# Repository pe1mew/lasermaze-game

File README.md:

# lasermaze-game
A laser maze game designed for BULA2022 

# Work in progress
This is work in progress. Thing may be added or changed without notice.

# Directions
The Architecture of the laser maze can be found [here](Architecture/architecture.md).

# Questions?
If you have any question? please raise an issue and I will ook in to it.

### Disclaimer
The lasermaze-game is distributed in the hope that it will be useful, but WITHOUT ANY WARRANTY; without even the 
implied warranty of MERCHANTABILITY or FITNESS FOR A PARTICULAR PURPOSE.
  
### License
The lasermaze-game is free software and hardware: 
you can redistribute it and/or modify it under the terms of a Creative Commons Attribution-NonCommercial 4.0 International License (http://creativecommons.org/licenses/by-nc/4.0/) by PE1MEW (http://pe1mew.nl) E-mail: pe1mew@pe1mew.nl

<br />This work is licensed under a <a rel="license" href="http://creativecommons.org/licenses/by-nc/4.0/">Creative Commons Attribution-NonCommercial 4.0 International License</a>.

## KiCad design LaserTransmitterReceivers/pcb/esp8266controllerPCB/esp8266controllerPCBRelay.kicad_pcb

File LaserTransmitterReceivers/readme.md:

# What to use, where to buy

The following links provide an example. Find the cheapest yourself!

## Transmitter
The laser transmitters are [KY-008 650nm Laser sensor Module 6mm 5V 5mW Red Laser Dot Diode Copper Head KY008](https://www.aliexpress.com/item/4000693969769.html?spm=a2g0o.cart.0.0.43a738dam0hMLE&mp=1) as can found Aliexpress or a equivalent.

## Receptor
For the receivers a LDR prototype board is used: [Photoresistor (LDR) Sensor Module Detects Light Sensitive Photodiode for Arduino](https://www.aliexpress.com/item/32452315745.html) as can found Aliexpress or a equivalent.

## Magnets
The magnets to stick the receptors and transmittors to a metal object are [Circular Magnets sheet 15mm X 6mm Round Neodymium Magnet Strong N35 15x6mm Permanent Disc Magnet 15*6 mm](https://www.aliexpress.com/item/1005001581640011.html) as can be found on Aliexpress.

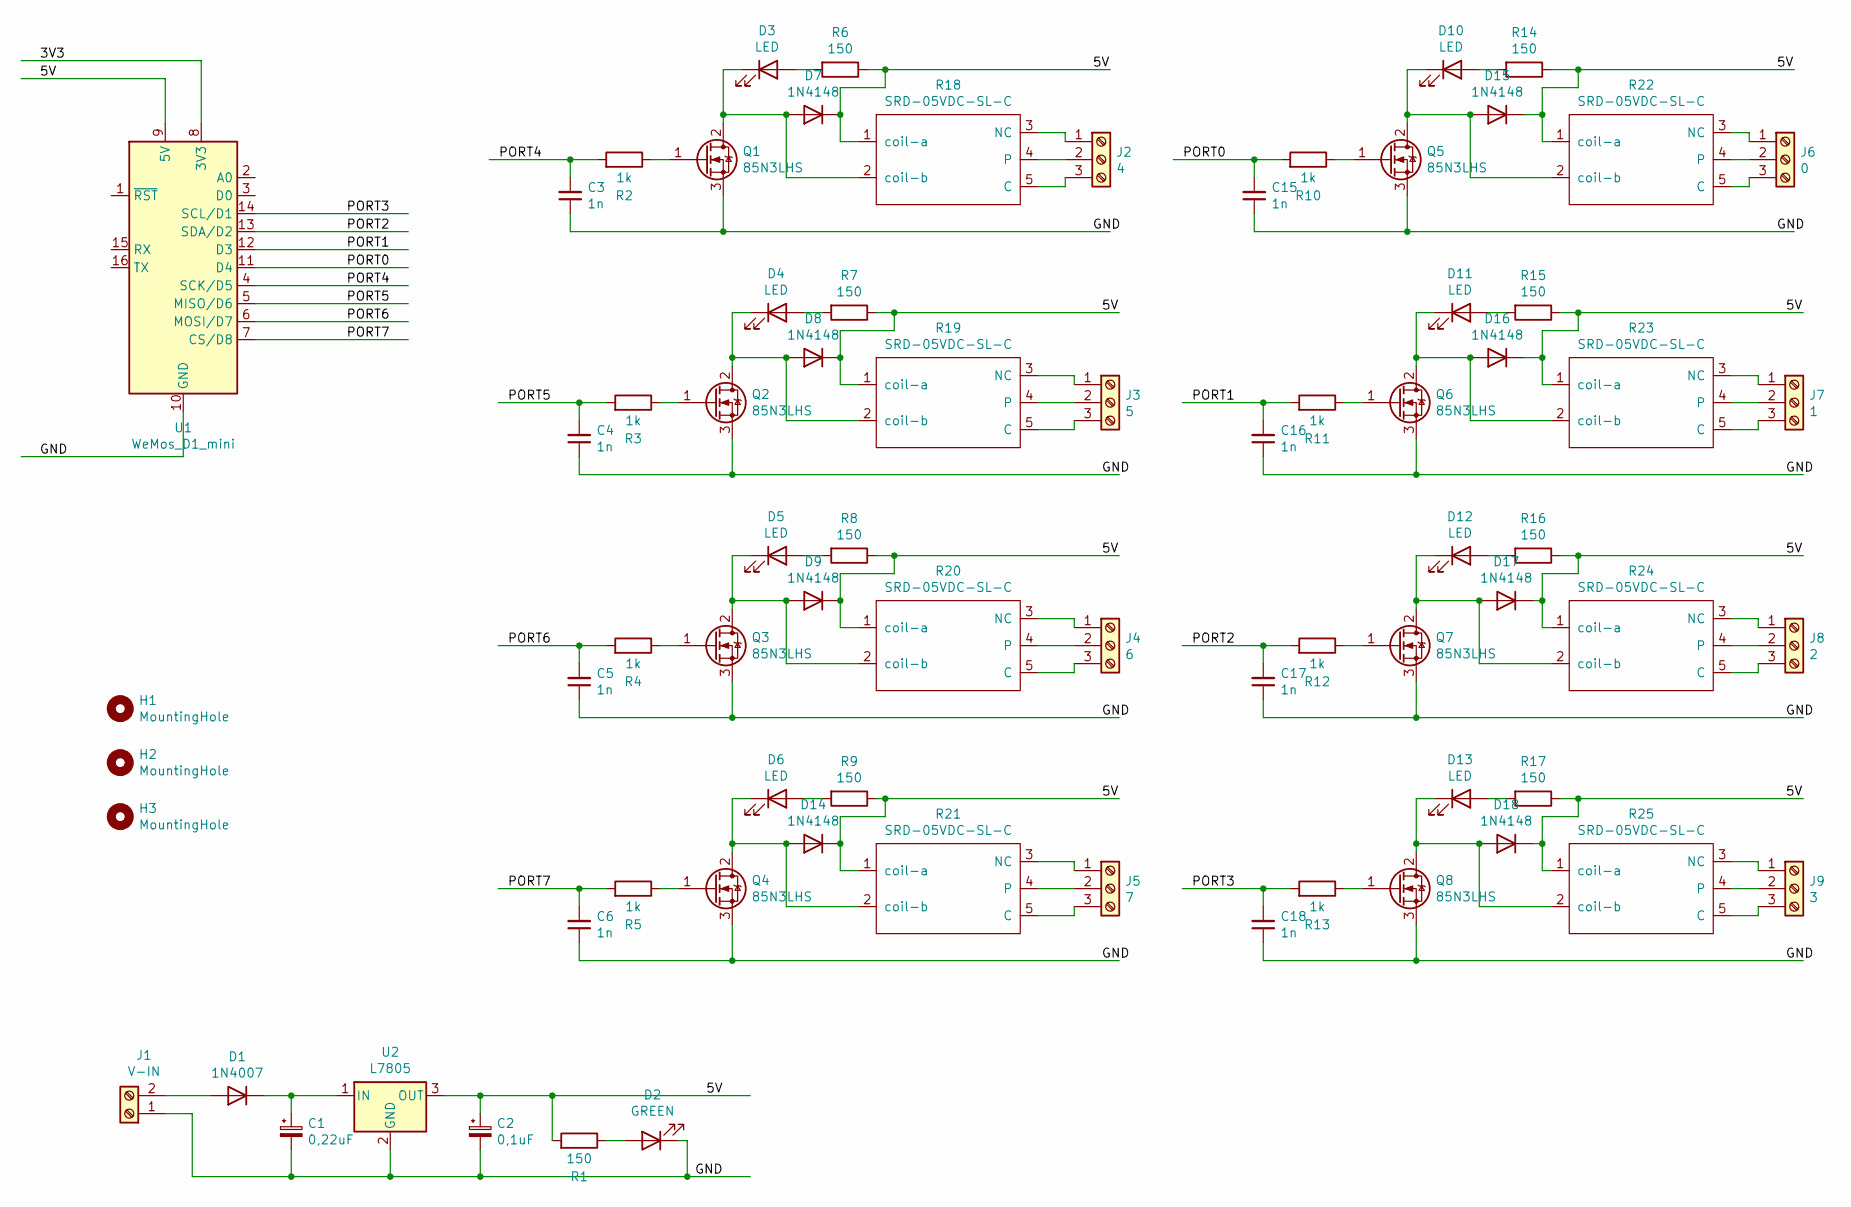
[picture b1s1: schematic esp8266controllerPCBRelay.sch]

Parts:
C1: 0,22uF; CP_Radial_D5.0mm_P2.00mm
C2: 0,1uF; CP_Radial_D5.0mm_P2.00mm
C3, C4, C5, C6, C15, C16, C17, C18: 1n; C_0805_2012Metric_Pad1.18x1.45mm_HandSolder
D1: 1N4007; D_DO-41_SOD81_P12.70mm_Horizontal
D2: GREEN; LED_0805_2012Metric_Pad1.15x1.40mm_HandSolder
D3, D4, D5, D6, D10, D11, D12, D13: LED; LED_0805_2012Metric_Pad1.15x1.40mm_HandSolder
D7, D8, D9, D14, D15, D16, D17, D18: 1N4148; D_DO-35_SOD27_P7.62mm_Horizontal
H1, H2, H3: MountingHole; MountingHole_6mm
J1: V-IN; TerminalBlock_Altech_AK300-2_P5.00mm
J2: 4; TerminalBlock_Altech_AK300-3_P5.00mm
J3: 5; TerminalBlock_Altech_AK300-3_P5.00mm
J4: 6; TerminalBlock_Altech_AK300-3_P5.00mm
J5: 7; TerminalBlock_Altech_AK300-3_P5.00mm
J6: 0; TerminalBlock_Altech_AK300-3_P5.00mm
J7: 1; TerminalBlock_Altech_AK300-3_P5.00mm
J8: 2; TerminalBlock_Altech_AK300-3_P5.00mm
J9: 3; TerminalBlock_Altech_AK300-3_P5.00mm
Q1, Q2, Q3, Q4, Q5, Q6, Q7, Q8: 85N3LHS; SIPAK_Vertical
R1, R6, R7, R8, R9, R14, R15, R16, R17: 150; R_0805_2012Metric_Pad1.20x1.40mm_HandSolder
R2, R3, R4, R5, R10, R11, R12, R13: 1k; R_0805_2012Metric_Pad1.20x1.40mm_HandSolder
R18, R19, R20, R21, R22, R23, R24, R25: SRD-05VDC-SL-C
U1: WeMos_D1_mini; WEMOS_D1_mini_light
U2: L7805; TO-220-3_Horizontal_TabDown

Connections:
/5V: C2.1, D7.1 (K), D8.1 (K), D9.1 (K), D14.1 (K), D15.1 (K), D16.1 (K), D17.1 (K), D18.1 (K), R1.2, R6.1, R7.1, R8.1, R9.1, R14.1, R15.1, R16.1, R17.1, R18.1 (coil-a), R19.1 (coil-a), R20.1 (coil-a), R21.1 (coil-a), R22.1 (coil-a), R23.1 (coil-a), R24.1 (coil-a), R25.1 (coil-a), U1.9 (5V), U2.3 (OUT)
/GND: C1.2, C2.2, C3.1, C4.1, C5.1, C6.1, C15.1, C16.1, C17.1, C18.1, D2.1 (K), J1.1, Q1.3 (S), Q2.3 (S), Q3.3 (S), Q4.3 (S), Q5.3 (S), Q6.3 (S), Q7.3 (S), Q8.3 (S), U1.10 (GND), U2.2 (GND)
/PORT0: C15.2, R10.2, U1.11 (D4)
/PORT1: C16.2, R11.2, U1.12 (D3)
/PORT2: C17.2, R12.2, U1.13 (SDA/D2)
/PORT3: C18.2, R13.2, U1.14 (SCL/D1)
/PORT4: C3.2, R2.2, U1.4 (SCK/D5)
/PORT5: C4.2, R3.2, U1.5 (MISO/D6)
/PORT6: C5.2, R4.2, U1.6 (MOSI/D7)
/PORT7: C6.2, R5.2, U1.7 (CS/D8)
unnamed: C1.1, D1.1 (K), U2.1 (IN)
unnamed: D1.2 (A), J1.2
unnamed: D2.2 (A), R1.1
unnamed: D3.1 (K), D7.2 (A), Q1.2 (D), R18.2 (coil-b)
unnamed: D3.2 (A), R6.2
unnamed: D4.1 (K), D8.2 (A), Q2.2 (D), R19.2 (coil-b)
unnamed: D4.2 (A), R7.2
unnamed: D5.1 (K), D9.2 (A), Q3.2 (D), R20.2 (coil-b)
unnamed: D5.2 (A), R8.2
unnamed: D6.2 (A), R9.2
unnamed: D10.1 (K), D15.2 (A), Q5.2 (D), R22.2 (coil-b)
unnamed: D10.2 (A), R14.2
unnamed: D11.1 (K), D16.2 (A), Q6.2 (D), R23.2 (coil-b)
unnamed: D11.2 (A), R15.2
unnamed: D12.1 (K), D17.2 (A), Q7.2 (D), R24.2 (coil-b)
unnamed: D12.2 (A), R16.2
unnamed: D13.1 (K), D18.2 (A), Q8.2 (D), R25.2 (coil-b)
unnamed: D13.2 (A), R17.2
unnamed: D6.1 (K), D14.2 (A), Q4.2 (D), R21.2 (coil-b)
unnamed: J2.1, R18.3 (NC)
unnamed: J2.2, R18.4
unnamed: J2.3, R18.5 (C)
unnamed: J3.1, R19.3 (NC)
unnamed: J3.2, R19.4
unnamed: J3.3, R19.5 (C)
unnamed: J4.1, R20.3 (NC)
unnamed: J4.2, R20.4
unnamed: J4.3, R20.5 (C)
unnamed: J5.1, R21.3 (NC)
unnamed: J5.2, R21.4
unnamed: J5.3, R21.5 (C)
unnamed: J6.1, R22.3 (NC)
unnamed: J6.2, R22.4
unnamed: J6.3, R22.5 (C)
unnamed: J7.1, R23.3 (NC)
unnamed: J7.2, R23.4
unnamed: J7.3, R23.5 (C)
unnamed: J8.1, R24.3 (NC)
unnamed: J8.2, R24.4
unnamed: J8.3, R24.5 (C)
unnamed: J9.1, R25.3 (NC)
unnamed: J9.2, R25.4
unnamed: J9.3, R25.5 (C)
unnamed: Q1.1 (G), R2.1
unnamed: Q2.1 (G), R3.1
unnamed: Q3.1 (G), R4.1
unnamed: Q4.1 (G), R5.1
unnamed: Q5.1 (G), R10.1
unnamed: Q6.1 (G), R11.1
unnamed: Q7.1 (G), R12.1
unnamed: Q8.1 (G), R13.1

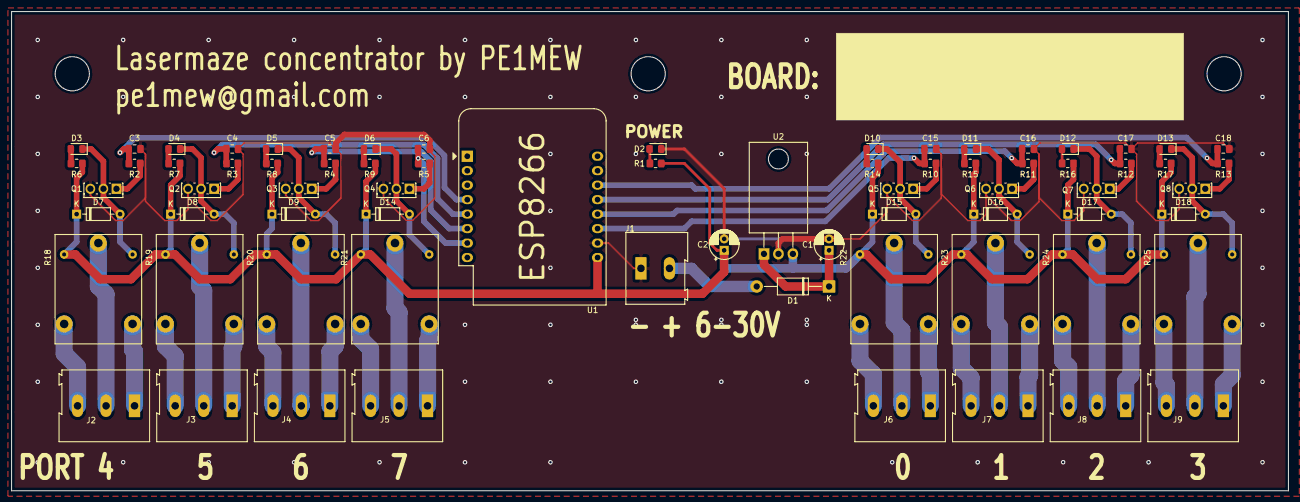
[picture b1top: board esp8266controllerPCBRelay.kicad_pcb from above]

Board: 2 copper layers, 224.2 x 84.1 mm, 75 parts (0 on the bottom side), 61 nets.

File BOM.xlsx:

| Reference | Quantity | totaal | Value | Footprint | aanwezig
Relay | C1 | 1 | 2 | 0,22uF | Capacitor_THT:CP_Radial_D5.0mm_P2.00mm
Relay | C3 C4 C5 C6 C15 C16 C17 C18 | 8 | 8 | 1n | Capacitor_SMD:C_0805_2012Metric_Pad1.18x1.45mm_HandSolder
Relay | C2 | 1 | 2 | 0,1uF | Capacitor_THT:CP_Radial_D5.0mm_P2.00mm
Relay | D1 | 1 | 1 | 1N4007 | Diode_THT:D_DO-41_SOD81_P12.70mm_Horizontal
Relay | D3 D4 D5 D6 D10 D11 D12 D13 | 8 | 8 | LED | LED_SMD:LED_0805_2012Metric_Pad1.15x1.40mm_HandSolder
Relay | D7 D8 D9 D14 D15 D16 D17 D18 | 8 | 16 | 1N4148 | Diode_THT:D_DO-35_SOD27_P7.62mm_Horizontal
Relay | D2 | 1 | 2 | GREEN | LED_SMD:LED_0805_2012Metric_Pad1.15x1.40mm_HandSolder
Relay | J1 - J9 | 9 | 9 | V-IN | TerminalBlock:TerminalBlock_Altech_AK300-2_P5.00mm
Relay | Q1 Q2 Q3 Q4 Q5 Q6 Q7 Q8 | 8 | 8 | 85N3LHS | Package_TO_SOT_THT:SIPAK_Vertical
Relay | R2 R3 R4 R5 R10 R11 R12 R13 | 8 | 8 | 1k | Resistor_SMD:R_0805_2012Metric_Pad1.20x1.40mm_HandSolder
Relay | R1 R6 R7 R8 R9 R14 R15 R16 R17 | 9 | 9 | 150ohm | Resistor_SMD:R_0805_2012Metric_Pad1.20x1.40mm_HandSolder
Relay | R18 R19 R20 R21 R22 R23 R24 R25 | 8 | 8 | SRD-05VDC-SL-C | components:SRD-05VDC-SL-C | 1
Relay | U1 | 1 | 2 | WeMos_D1_mini | Module:WEMOS_D1_mini_light | 1
Relay | U2 | 1 | 2 | L7805 | Package_TO_SOT_THT:TO-220-3_Horizontal_TabDown
InOut | C1 | 1 | 2 | 0,22uF | Capacitor_THT:CP_Radial_D5.0mm_P2.00mm
InOut | C2 | 1 | 2 | 0,1uF | Capacitor_THT:CP_Radial_D5.0mm_P2.00mm
InOut | C3 C4 C5 C6 C7 C8 C9 C10 C11 C12 C13 C14 C15 C16 C17 C18 C19 C20 C21 C22 C23 C2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 | 24 | 24 | 1n | Capacitor_SMD:C_0805_2012Metric_Pad1.18x1.45mm_HandSolder
InOut | D1 | 1 | 2 | 1N4007 | Diode_THT:D_DO-41_SOD81_P12.70mm_Horizontal
Output | D3 D4 D5 D6 D10 D11 D12 D13 | 8 | 8 | LED | LED_SMD:LED_0805_2012Metric_Pad1.15x1.40mm_HandSolder
Output | D7 D8 D9 D14 D15 D16 D17 | 7 | 7 | BAT54S | Package_TO_SOT_SMD:SOT-23
InOut | D2 | 1 | 2 | GREEN | LED_SMD:LED_0805_2012Metric_Pad1.15x1.40mm_HandSolder
Always | J1-J9 | 9 | 18 | V-IN | TerminalBlock:TerminalBlock_Altech_AK300-2_P5.00mm
InOut | JP1 JP2 JP3 JP4 JP5 JP6 JP7 | 7 | 14 | inputEnable | Jumpers:SMT-JUMPER_2_NO_SILK
Output | Q1 Q2 Q3 Q4 Q5 Q6 Q7 Q8 | 8 | 8 | 85N3LHS | Package_TO_SOT_THT:SIPAK_Vertical
Output | R2 R3 R4 R5 R10 R11 R12 R13 | 8 | 8 | 1k | Resistor_SMD:R_0805_2012Metric_Pad1.20x1.40mm_HandSolder
Output | R1 R6 R7 R8 R9 R14 R15 R16 R17 | 9 | 9 | 150 | Resistor_SMD:R_0805_2012Metric_Pad1.20x1.40mm_HandSolder
InOut | U1 | 1 | 2 | WeMos_D1_mini | Module:WEMOS_D1_mini_light | 1
InOut | U2 | 1 | 2 | L7805 | Package_TO_SOT_THT:TO-220-3_Horizontal_TabDown

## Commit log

2021-03-31 Initial commit and added STL-files for laser transmitters and receptors
2021-04-04 Addes Arduni environment
2021-04-05 Added some documentation
2021-04-10 Added image and MQTT bridge
2021-12-19 Development stages
2021-12-19 Add initial TX
2022-05-06 Added wifi-mqtt-example
2022-05-07 rescue update
2022-05-07 Update pre test rx function
2022-05-07 Cleanup
2022-05-07 Intermediate update
2022-05-07 First release of TX and RX
2022-05-08 Moved info to final location
2022-05-08 Final Move
2022-05-08 Added KiCad PCB
2022-05-10 Added Relay PCB
2022-05-22 Added BOM
2022-06-04 Added response message to set port on TX controller
2022-06-04 correction
2022-06-04 Added watchdog to RC controller
2022-06-04 Added watchdog to RC controller Corrected code
2022-06-04 Corrected
2022-06-18 Added connector
2022-06-18 Added nodeRed repo
2022-07-09 changed file name
2022-07-29 Added mosaic page,
2022-07-31 Minor update
2022-07-31 Added relay software for relay concentrator
2022-12-10 Added images and references to laser and LDR
2022-12-10 Added architecture
